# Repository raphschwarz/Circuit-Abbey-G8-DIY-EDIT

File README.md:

# Circuit-Abbey-G8-DIY-EDIT
diy edit for Circuit Abbaye G8 clock divider eurorack module

JACKS CHANGED FOR THONKIKONS

ATMEGA164 package changed to TQFP44//

crystal is thru-hole

MAY2018//74AC244/74LS244 line driver footprint changed to a wider TSSOP to fit most 74LS244 wich are in a wider tssop20 package. 
should still work with the original part (74AC244MTC-ND) but also should fit the more common (SN74LS244DBR)

AUGUST2018// switch has been replaced by TL1105SP (612-TL1105SP-250) as on mutable instruments modules to match thonkikonn jacks height

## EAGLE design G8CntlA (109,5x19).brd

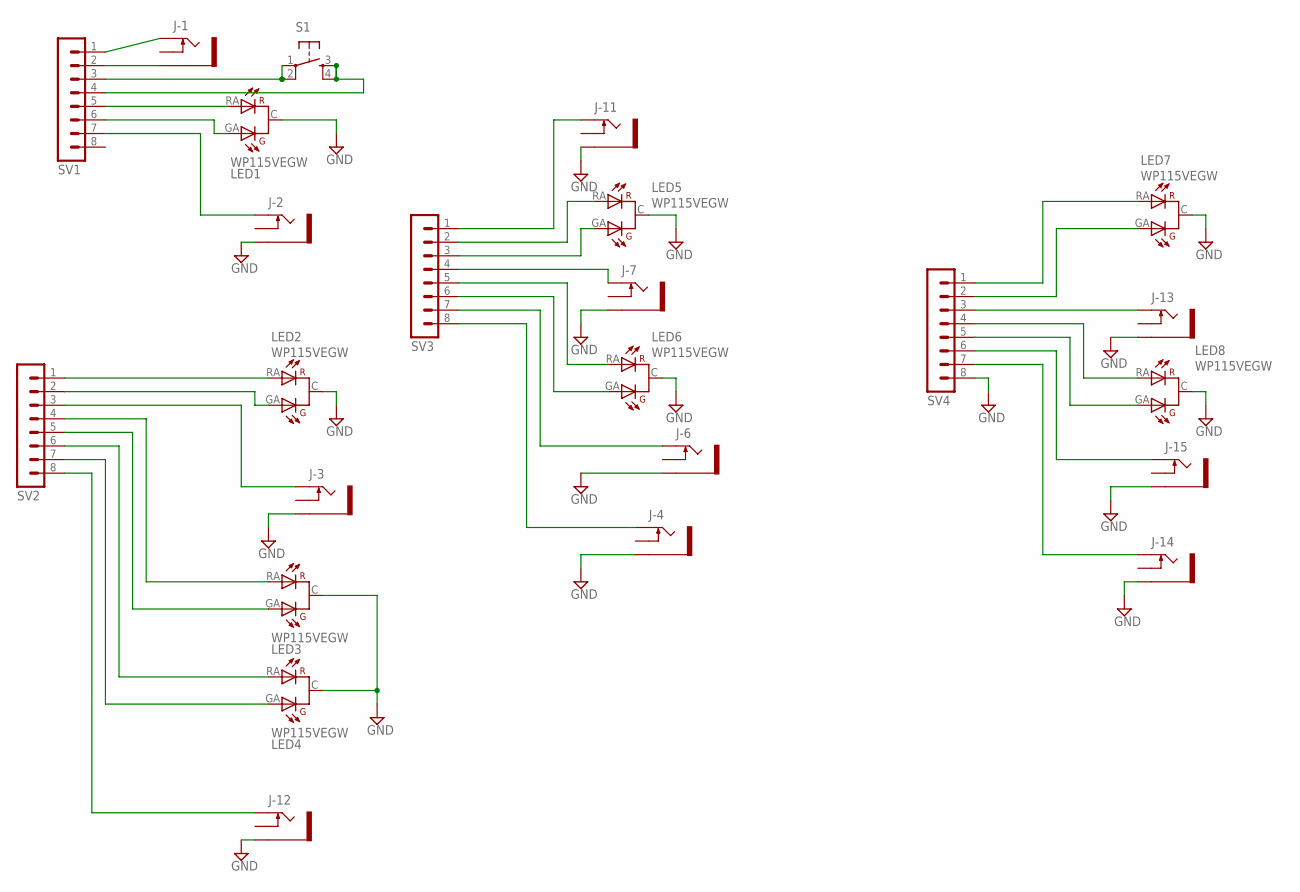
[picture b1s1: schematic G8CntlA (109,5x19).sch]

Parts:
J-1, J-2, J-3, J-4, J-6, J-7, J-11, J-12, J-13, J-14, J-15: THONKICONNNEW; WQP-PJ301M-12_JACK
LED1, LED2, LED3, LED4, LED5, LED6, LED7, LED8: WP115VEGW
S1: SPARKFUN_TAC_SWITCHPTH; SPARKFUN_TACTILE-PTH
SV1, SV2, SV3, SV4: MA08-1-O; MA08-OCT

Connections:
GND: J-2.P$3_SLEEVE (SLEEVE), J-3.P$3_SLEEVE (SLEEVE), J-4.P$3_SLEEVE (SLEEVE), J-6.P$3_SLEEVE (SLEEVE), J-7.P$3_SLEEVE (SLEEVE), J-11.P$3_SLEEVE (SLEEVE), J-12.P$3_SLEEVE (SLEEVE), J-13.P$3_SLEEVE (SLEEVE), J-14.P$3_SLEEVE (SLEEVE), J-15.P$3_SLEEVE (SLEEVE), LED1.C, LED2.C, LED3.C, LED4.C, LED5.C, LED6.C, LED7.C, LED8.C, SV4.8
unnamed: S1.1, S1.2, SV1.3
unnamed: S1.3, S1.4, SV1.4
unnamed: LED2.RA (GA), SV2.1
unnamed: J-1.P$1_TIP (TIP), SV1.1
unnamed: J-1.P$3_SLEEVE (SLEEVE), SV1.2
unnamed: J-2.P$1_TIP (TIP), SV1.7
unnamed: LED1.RA (GA), SV1.5
unnamed: LED1.GA (RA), SV1.6
unnamed: LED2.GA (RA), SV2.2
unnamed: J-3.P$1_TIP (TIP), SV2.3
unnamed: LED3.RA (GA), SV2.4
unnamed: LED3.GA (RA), SV2.5
unnamed: J-12.P$1_TIP (TIP), SV2.8
unnamed: LED4.RA (GA), SV2.6
unnamed: LED4.GA (RA), SV2.7
unnamed: J-11.P$1_TIP (TIP), SV3.1
unnamed: LED5.RA (GA), SV3.2
unnamed: LED5.GA (RA), SV3.3
unnamed: J-7.P$1_TIP (TIP), SV3.4
unnamed: LED6.RA (GA), SV3.5
unnamed: LED6.GA (RA), SV3.6
unnamed: J-6.P$1_TIP (TIP), SV3.7
unnamed: J-4.P$1_TIP (TIP), SV3.8
unnamed: J-15.P$1_TIP (TIP), SV4.6
unnamed: J-13.P$1_TIP (TIP), SV4.3
unnamed: J-14.P$1_TIP (TIP), SV4.7
unnamed: LED7.RA (GA), SV4.1
unnamed: LED7.GA (RA), SV4.2
unnamed: LED8.RA (GA), SV4.4
unnamed: LED8.GA (RA), SV4.5

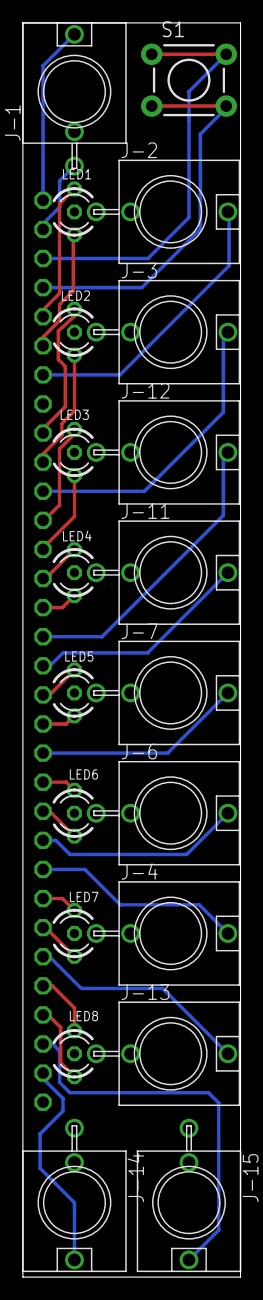
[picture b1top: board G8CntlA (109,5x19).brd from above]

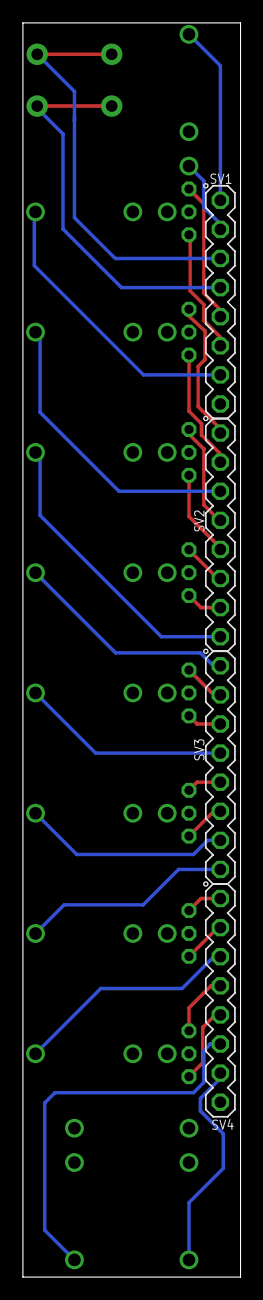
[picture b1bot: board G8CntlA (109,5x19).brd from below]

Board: 2 copper layers, 19.0 x 109.5 mm, 24 parts (4 on the bottom side), 31 nets.

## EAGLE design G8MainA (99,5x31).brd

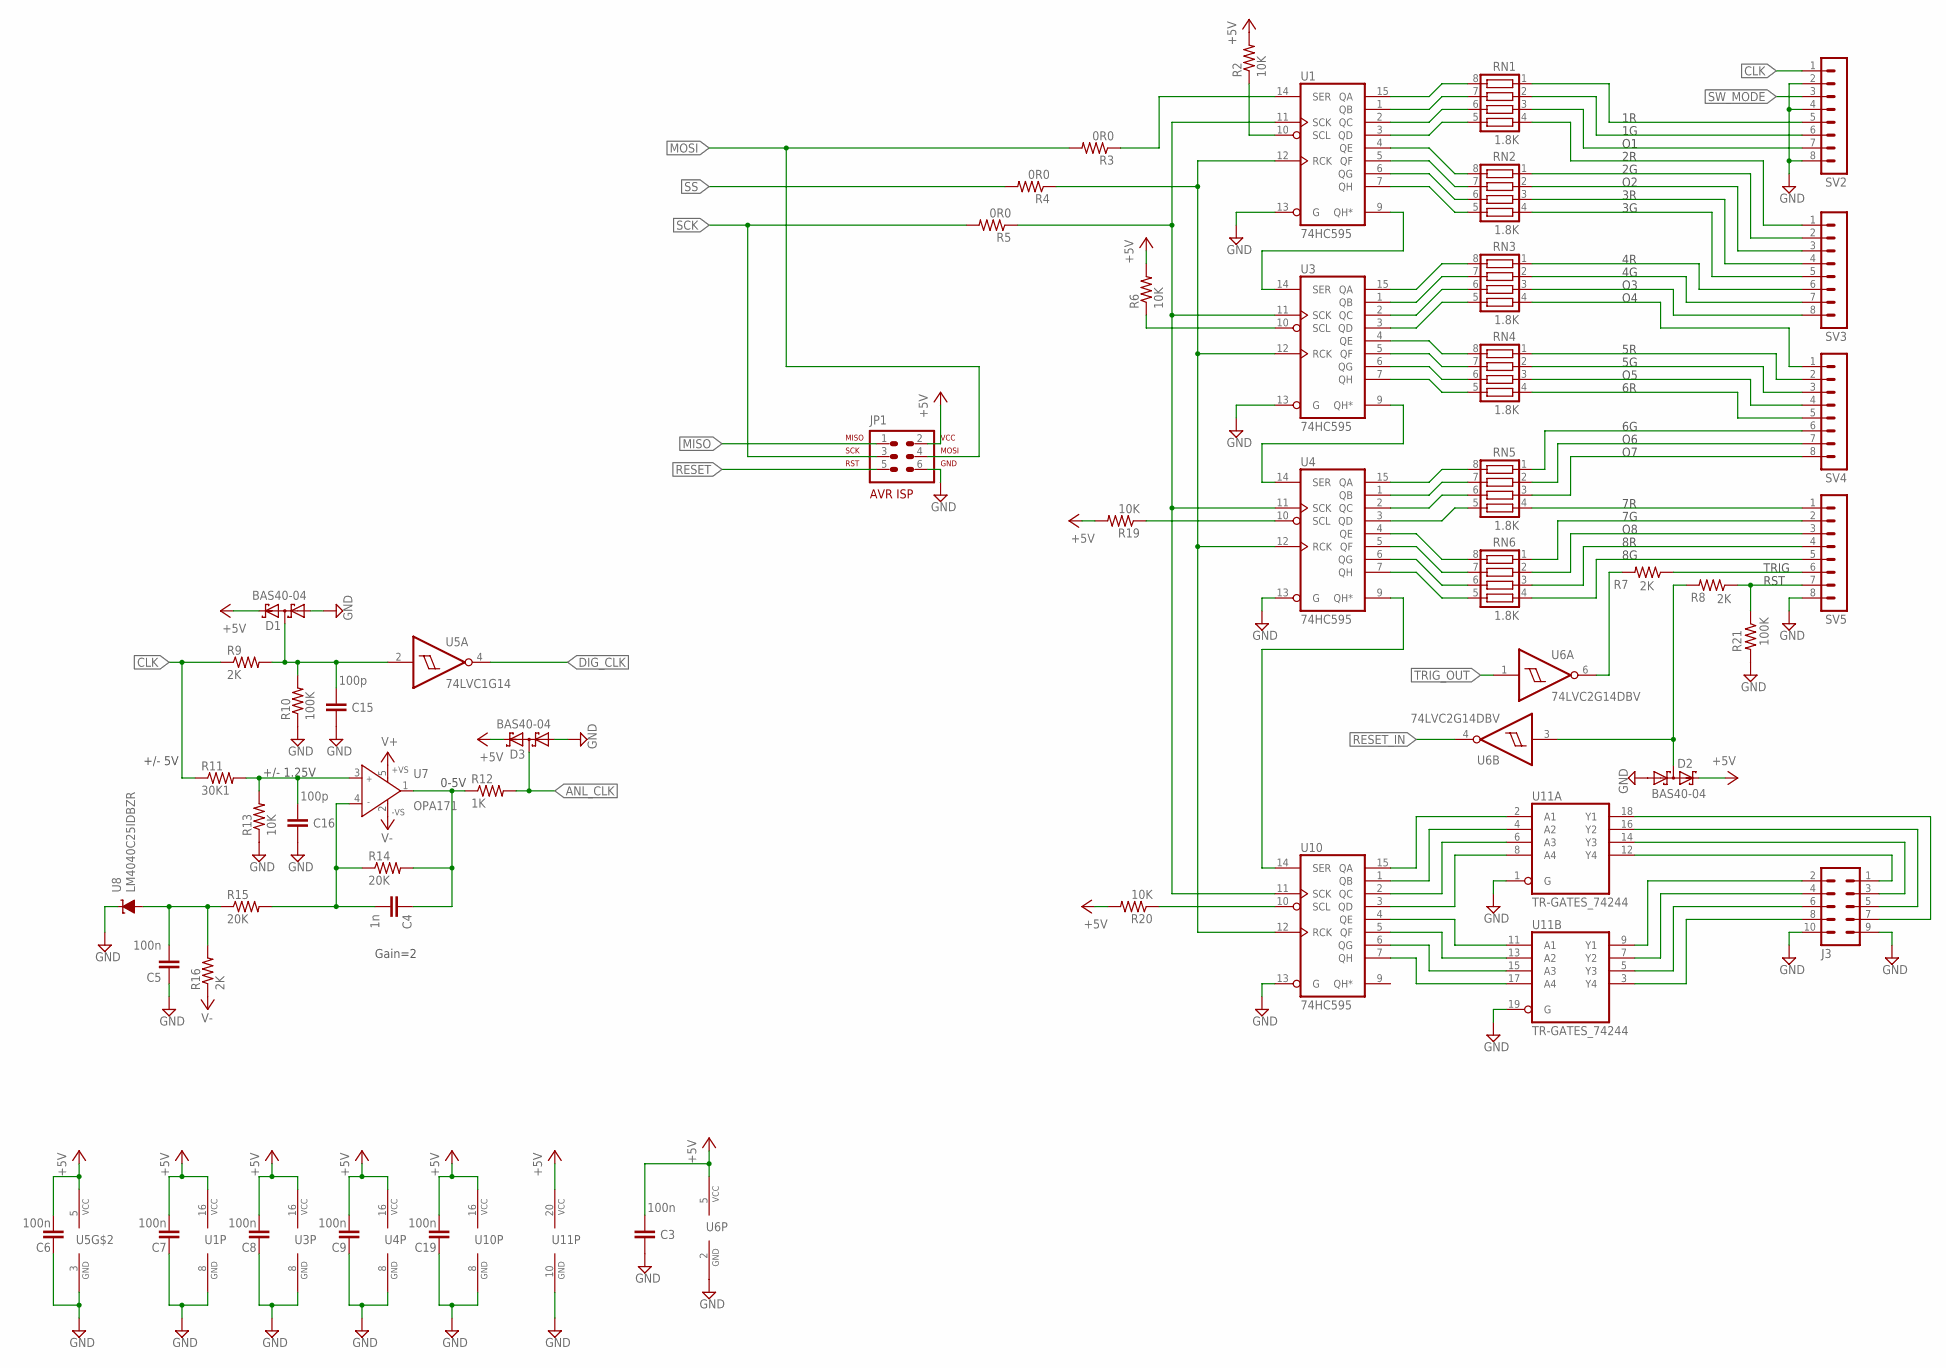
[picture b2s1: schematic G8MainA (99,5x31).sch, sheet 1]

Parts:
C3, C5, C6, C7, C8, C9, C19: 100n; C0603
C4: 1n; C0603
C15, C16: 100p; C0603
D1, D2, D3: BAS40-04; SOT23
J3: MA05-2
JP1: AVR-ISP-6VERT; AVR-ISP-6
R2, R6, R13, R19, R20: 10K; R0603
R3, R4, R5: 0R0; R0603
R7, R8, R9, R16: 2K; R0603
R10, R21: 100K; R0603
R11: 30K1; R0603
R12: 1K; R0603
R14, R15: 20K; R0603
RN1, RN2, RN3, RN4, RN5, RN6: 1.8K; CTS742C083
SV2, SV3, SV4, SV5: MA08-1-O; MA08-OCT
U1, U3, U4, U10: 74HC595; TSSOP16
U5: 74LVC1G14; SOT23-5L
U6: 74LVC2G14DBV; SOT23-6
U7: OPA171; SOT23-5
U8: LM4040C25IDBZR; DBZ_R-PDSO-G3
U11: TR-GATES_74244; TR-GATES_TSSOP20

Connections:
+5V: C3.2, C6.2, C7.2, C8.2, C9.2, C19.2, D1.2 (C2), D2.2 (C2), D3.2 (C2), JP1.2, R2.2, R6.2, R19.2, R20.2, U1.16 (VCC), U3.16 (VCC), U4.16 (VCC), U5.5 (VCC), U6.5 (VCC), U10.16 (VCC), U11.20 (VCC); also elsewhere on the board
ANL_CLK: D3.3 (C1A2), R12.2; also elsewhere on the board
CLK: R9.1, R11.1, SV2.1
DIG_CLK: U5.4 (O); also elsewhere on the board
GND: C3.1, C5.1, C6.1, C7.1, C8.1, C9.1, C15.1, C16.1, C19.1, D1.1 (A1), D2.1 (A1), D3.1 (A1), J3.9, J3.10, JP1.6, R10.1, R13.1, R21.2, SV2.2, SV2.4, SV2.8, SV5.8, U1.8 (GND), U1.13 (G), U3.8 (GND), U3.13 (G), U4.8 (GND), U4.13 (G), U5.3 (GND), U6.2 (GND), U8.1 (C), U10.8 (GND), U10.13 (G), U11.1 (G), U11.10 (GND), U11.19 (G); also elsewhere on the board
MISO: JP1.1; also elsewhere on the board
MOSI: JP1.4, R3.2; also elsewhere on the board
unnamed: U1.9 (QH*), U3.14 (SER)
unnamed: C15.2, D1.3 (C1A2), R9.2, R10.2, U5.2 (I)
unnamed: C16.2, R11.2, R13.2, U7.3 (IN+)
unnamed: C4.2, R14.1, R15.2, U7.4 (IN-)
unnamed: U3.9 (QH*), U4.14 (SER)
unnamed: R5.1, U1.11 (SCK), U3.11 (SCK), U4.11 (SCK), U10.11 (SCK)
unnamed: R4.1, U1.12 (RCK), U3.12 (RCK), U4.12 (RCK), U10.12 (RCK)
unnamed: R6.1, U3.10 (SCL)
unnamed: RN3.8, U3.15 (QA)
unnamed: RN2.8, U1.4 (QE)
unnamed: RN2.7, U1.5 (QF)
unnamed: RN2.6, U1.6 (QG)
unnamed: RN2.5, U1.7 (QH)
unnamed: RN1.5, U1.3 (QD)
unnamed: RN1.6, U1.2 (QC)
unnamed: C4.1, R12.1, R14.2, U7.1 (OUT)
unnamed: RN1.7, U1.1 (QB)
unnamed: RN1.8, U1.15 (QA)
unnamed: R3.1, U1.14 (SER)
unnamed: RN3.7, U3.1 (QB)
unnamed: RN3.6, U3.2 (QC)
unnamed: RN3.5, U3.3 (QD)
unnamed: RN4.8, U3.4 (QE)
unnamed: RN4.7, U3.5 (QF)
unnamed: RN4.6, U3.6 (QG)
unnamed: RN4.5, U3.7 (QH)
unnamed: RN5.8, U4.15 (QA)
unnamed: RN5.7, U4.1 (QB)
unnamed: RN5.6, U4.2 (QC)
unnamed: RN5.5, U4.3 (QD)
unnamed: RN6.8, U4.4 (QE)
unnamed: RN6.7, U4.5 (QF)
unnamed: RN6.6, U4.6 (QG)
unnamed: RN6.5, U4.7 (QH)
unnamed: RN1.1, SV2.5
unnamed: RN1.2, SV2.6
unnamed: RN1.3, SV2.7
unnamed: RN1.4, SV3.1
unnamed: RN2.1, SV3.2
unnamed: RN2.2, SV3.3
unnamed: RN2.3, SV3.4
unnamed: RN2.4, SV3.5
unnamed: RN3.1, SV3.6
unnamed: RN3.2, SV3.7
unnamed: RN3.3, SV3.8
unnamed: RN3.4, SV4.1
unnamed: RN4.1, SV4.2
unnamed: RN4.2, SV4.3
unnamed: RN4.3, SV4.4
unnamed: RN4.4, SV4.5
unnamed: RN5.1, SV4.6
unnamed: RN5.2, SV4.7
unnamed: RN5.3, SV4.8
unnamed: RN5.4, SV5.1
unnamed: RN6.1, SV5.2
unnamed: RN6.2, SV5.3
unnamed: RN6.3, SV5.4
unnamed: RN6.4, SV5.5
unnamed: R19.1, U4.10 (SCL)
unnamed: R2.1, U1.10 (SCL)
unnamed: C5.2, R15.1, R16.2, U8.2 (A)
unnamed: R8.1, R21.1, SV5.7
unnamed: R7.1, SV5.6
unnamed: R7.2, U6.6 (O)
unnamed: D2.3 (C1A2), R8.2, U6.3 (I)
unnamed: U4.9 (QH*), U10.14 (SER)
unnamed: R20.1, U10.10 (SCL)
unnamed: J3.7, U11.18 (Y1)
unnamed: U10.15 (QA), U11.2 (A1)
unnamed: U10.1 (QB), U11.4 (A2)
unnamed: U10.2 (QC), U11.6 (A3)
unnamed: U10.3 (QD), U11.8 (A4)
unnamed: U10.4 (QE), U11.11 (A1)
unnamed: U10.5 (QF), U11.13 (A2)
unnamed: U10.6 (QG), U11.15 (A3)
unnamed: U10.7 (QH), U11.17 (A4)
unnamed: J3.5, U11.16 (Y2)
unnamed: J3.3, U11.14 (Y3)
unnamed: J3.1, U11.12 (Y4)
unnamed: J3.2, U11.9 (Y1)
unnamed: J3.4, U11.7 (Y2)
unnamed: J3.6, U11.5 (Y3)
unnamed: J3.8, U11.3 (Y4)
RESET: JP1.5; also elsewhere on the board
RESET_IN: U6.4 (O); also elsewhere on the board
SCK: JP1.3, R5.2; also elsewhere on the board
SS: R4.2; also elsewhere on the board
SW_MODE: SV2.3; also elsewhere on the board
TRIG_OUT: U6.1 (I); also elsewhere on the board
V+: U7.5 (+VS); also elsewhere on the board
V-: R16.1, U7.2 (-VS); also elsewhere on the board

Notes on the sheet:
+/- 5V
+/- 1.25V
Gain=2
0-5V
TRIG
RST

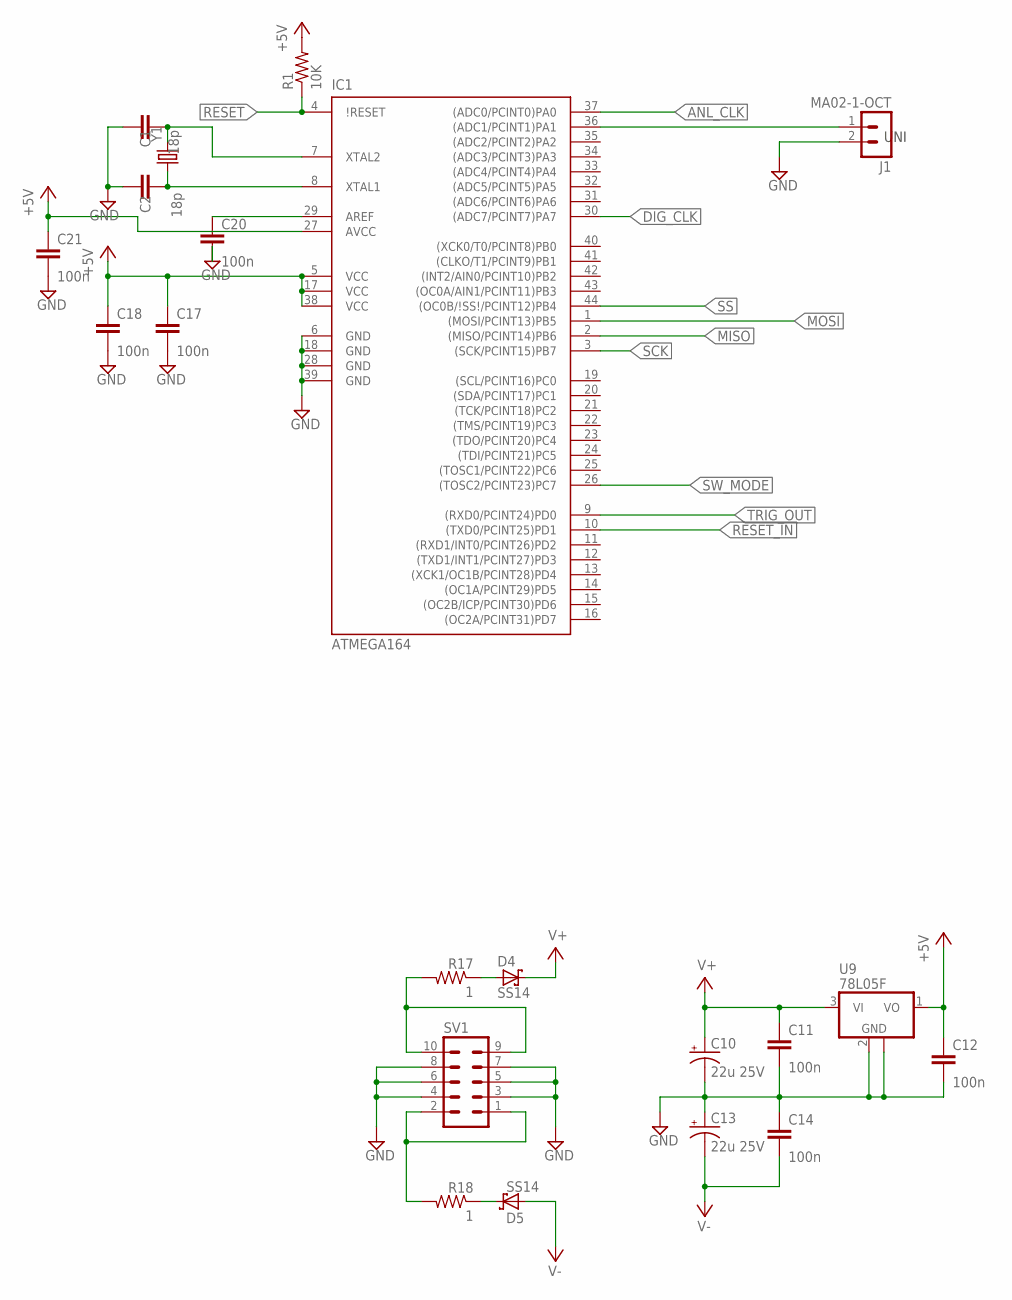
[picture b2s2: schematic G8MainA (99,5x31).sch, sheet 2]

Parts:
C1, C2: 18p; C0603
C10, C13: 22u 25V; PANASONIC_C
C11, C12, C14, C17, C18, C20, C21: 100n; C0603
D4, D5: SS14; SMA-DO214AC
IC1: ATMEGA164; TQFP44
J1: MA02-1-OCT
R1: 10K; R0603
R17, R18: 1; R0603
SV1: MA05-2
U9: 78L05F; SOT89
Y1: CRYSTALHC49UV; HC49U-V

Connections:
+5V: C12.1, C17.1, C18.1, C21.1, IC1.5 (VCC), IC1.17 (VCC), IC1.27 (AVCC), IC1.38 (VCC), R1.2, U9.1 (VO); also elsewhere on the board
ANL_CLK: IC1.37 ((ADC0/PCINT0)PA0); also elsewhere on the board
DIG_CLK: IC1.30 ((ADC7/PCINT7)PA7); also elsewhere on the board
GND: C1.1, C2.1, C10.-, C11.2, C12.2, C13.+, C14.1, C17.2, C18.2, C20.2, C21.2, IC1.6 (GND), IC1.18 (GND), IC1.28 (GND), IC1.39 (GND), J1.2, SV1.3, SV1.4, SV1.5, SV1.6, SV1.7, SV1.8, U9.2 (GND), U9.2@1 (GND); also elsewhere on the board
MISO: IC1.2 ((MISO/PCINT14)PB6); also elsewhere on the board
MOSI: IC1.1 ((MOSI/PCINT13)PB5); also elsewhere on the board
unnamed: C20.1, IC1.29 (AREF)
unnamed: C2.2, IC1.8 (XTAL1), Y1.1
unnamed: C1.2, IC1.7 (XTAL2), Y1.2
unnamed: IC1.36 ((ADC1/PCINT1)PA1), J1.1
unnamed: R18.2, SV1.1, SV1.2
unnamed: D4.A, R17.1
unnamed: R17.2, SV1.9, SV1.10
unnamed: D5.K (C), R18.1
RESET: IC1.4 (\!RESET), R1.1; also elsewhere on the board
RESET_IN: IC1.10 ((TXD0/PCINT25)PD1); also elsewhere on the board
SCK: IC1.3 ((SCK/PCINT15)PB7); also elsewhere on the board
SS: IC1.44 ((OC0B/\!SS\!/PCINT12)PB4); also elsewhere on the board
SW_MODE: IC1.26 ((TOSC2/PCINT23)PC7); also elsewhere on the board
TRIG_OUT: IC1.9 ((RXD0/PCINT24)PD0); also elsewhere on the board
V+: C10.+, C11.1, D4.K (C), U9.3 (VI); also elsewhere on the board
V-: C13.-, C14.2, D5.A; also elsewhere on the board

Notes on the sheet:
UNI

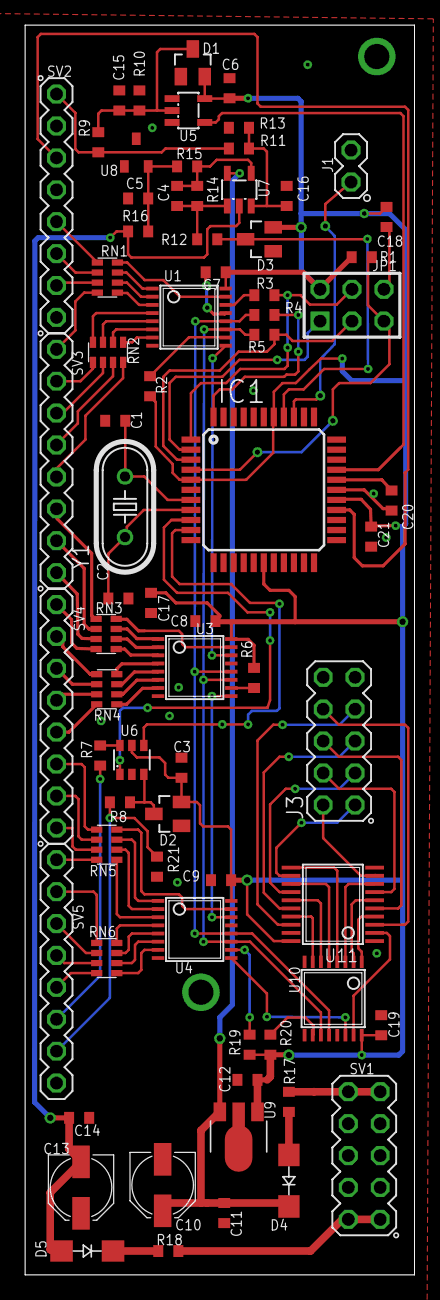
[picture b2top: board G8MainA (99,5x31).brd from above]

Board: 2 copper layers, 31.0 x 99.5 mm, 73 parts (0 on the bottom side), 106 nets.

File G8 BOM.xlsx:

Part | Value | Device | Package | Description | CA | DK | MF | MOUSER | MPN | OC_FARNELL | OC_NEWARK | VALUE
C1 | 18p | C0603 | C0603
C2 | 18p | C0603 | C0603
C3 | 100n | C0603 | C0603
C4 | 1n | C0603 | C0603
C5 | 100n | C0603 | C0603
C6 | 100n | C0603 | C0603
C7 | 100n | C0603 | C0603
C8 | 100n | C0603 | C0603
C9 | 100n | C0603 | C0603
C10 | 22u 25V | CPOL-USC | PANASONIC_C | POLARIZED CAPACITOR, American symbol |  | PCE3900CT-ND
C11 | 100n | C0603 | C0603
C12 | 100n | C0603 | C0603
C13 | 22u 25V | CPOL-USC | PANASONIC_C | POLARIZED CAPACITOR, American symbol |  | PCE3900CT-ND
C14 | 100n | C0603 | C0603
C15 | 100p | C0603 | C0603
C16 | 100p | C0603 | C0603
C17 | 100n | C0603 | C0603
C18 | 100n | C0603 | C0603
C19 | 100n | C0603 | C0603
C20 | 100n | C0603 | C0603
C21 | 100n | C0603 | C0603
D1 | BAS40-04 | BAS40-04 | SOT23 | Silicon Schottky Diodes
D2 | BAS40-04 | BAS40-04 | SOT23 | Silicon Schottky Diodes
D3 | BAS40-04 | BAS40-04 | SOT23 | Silicon Schottky Diodes
D4 | SS14 | T100331 | SMA-DO214AC | SS14 Schottky diode | T100331 |  |  |  |  |  |  | SS14
D5 | SS14 | T100331 | SMA-DO214AC | SS14 Schottky diode | T100331 |  |  |  |  |  |  | SS14
J1 | MA02-1-OCT | MA02-1-OCT | MA02-1-OCT
J3 |  | MA05-2 | MA05-2 | PIN HEADER
JP1 | AVR-ISP-6VERT | AVR-ISP-6VERT | AVR-ISP-6 | AVR ISP-6 Serial Programming Header
Q1 | 20M | TXC_7A | TXC_7A | Crystal 5x3.2 SMD |  |  |  | 717-7A-20.000MAAJ-T
R1 | 10K | R0603 | R0603
R2 | 10K | R0603 | R0603
R3 | 0R0 | R0603 | R0603
R4 | 0R0 | R0603 | R0603
R5 | 0R0 | R0603 | R0603
R6 | 10K | R0603 | R0603
R7 | 2K | R0603 | R0603
R8 | 2K | R0603 | R0603
R9 | 2K | R0603 | R0603
R10 | 100K | R0603 | R0603
R11 | 30K1 | R0603 | R0603
R12 | 1K | R0603 | R0603
R13 | 10K | R0603 | R0603
R14 | 20K | R0603 | R0603
R15 | 20K | R0603 | R0603
R16 | 2K | R0603 | R0603
R17 | 1.0 | R0603 | R0603
R18 | 1.0 | R0603 | R0603
R19 | 10K | R0603 | R0603
R20 | 10K | R0603 | R0603
R21 | 100K | R0603 | R0603
RN1 | 1.8K | CTS742C083 | CTS742C083 | Chip Resistor Array 4 Single Resistor |  |  |  |  |  | unknown | unknown
RN2 | 1.8K | CTS742C083 | CTS742C083 | Chip Resistor Array 4 Single Resistor |  |  |  |  |  | unknown | unknown
RN3 | 1.8K | CTS742C083 | CTS742C083 | Chip Resistor Array 4 Single Resistor |  |  |  |  |  | unknown | unknown
RN4 | 1.8K | CTS742C083 | CTS742C083 | Chip Resistor Array 4 Single Resistor |  |  |  |  |  | unknown | unknown
RN5 | 1.8K | CTS742C083 | CTS742C083 | Chip Resistor Array 4 Single Resistor |  |  |  |  |  | unknown | unknown
RN6 | 1.8K | CTS742C083 | CTS742C083 | Chip Resistor Array 4 Single Resistor |  |  |  |  |  | unknown | unknown
SV1 |  | MA05-2 | MA05-2 | PIN HEADER
SV2 |  | MA08-1-O | MA08-OCT | PIN HEADER
SV3 |  | MA08-1-O | MA08-OCT | PIN HEADER
SV4 |  | MA08-1-O | MA08-OCT | PIN HEADER
SV5 |  | MA08-1-O | MA08-OCT | PIN HEADER
U1 | 74HC595 | 74595DT | TSSOP16 | 8-bit SHIFT REGISTER, output latch
U2 | ATMEGA164-20M | ATMEGA644-20M | MLF44 | MICROCONTROLLER
U3 | 74HC595 | 74595DT | TSSOP16 | 8-bit SHIFT REGISTER, output latch
U4 | 74HC595 | 74595DT | TSSOP16 | 8-bit SHIFT REGISTER, output latch
U5 | 74LVC1G14 | 74LVC1G14 | SOT23-5L
U6 | 74LVC2G14DBV | 74LVC2G14DBV | SOT23-6
U7 | OPA171 | AD8031RJ | SOT23-5 | 2.7 V, 800 ?A, 80 MHz Rail-to-Rail I/O Amplifiers |  |  |  |  | AD8031ARTZ-REEL7 | 1660972.0 | 84R8399
U8 | LM4040C25IDBZR | LM4041A12DBZ | DBZ_R-PDSO-G3 | PRECISION MICROPOWER SHUNT VOLTAGE REFERENCE |  |  |  |  | LM4041A12IDBZR | 1407949.0 | 58K5875
U9 | 78L05F | 78L05F | SOT89 | POSITOIV-VOLTAGE REGULATORS
U10 | 74HC595 | 74595DT | TSSOP16 | 8-bit SHIFT REGISTER, output latch
U11 | 74244.0 | 74244.0 | TSSOP20 | Octal BUFFER and LINE DRIVER, 3-state
Switch |  | TL1105SPF250Q |  | 612-TL1105SP-250
Switch Cap |  |  | White | 612-1RWHT

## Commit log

2018-08-05 Add files via upload
    replaced switch

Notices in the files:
parts and their libraries:
SparkFun-FreqCtrl: Licensing: CC v3.0 Share-Alike You are welcome to use this library for commercial purposes.
